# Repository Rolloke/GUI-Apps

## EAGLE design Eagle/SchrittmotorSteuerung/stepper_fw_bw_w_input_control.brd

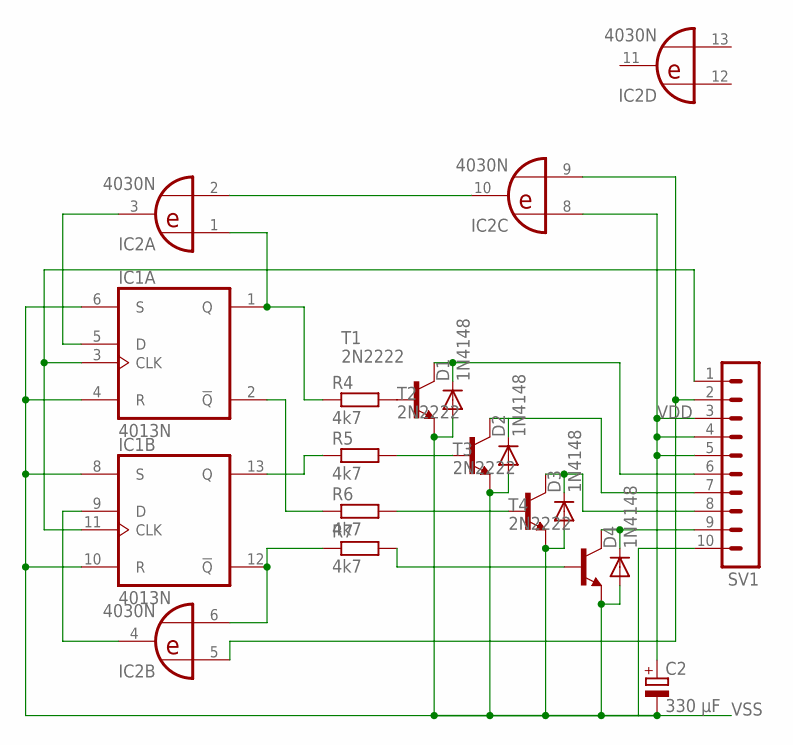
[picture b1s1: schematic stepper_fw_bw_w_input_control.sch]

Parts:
C2: 330 µF; E2,5-5
D1, D2, D3, D4: 1N4148; D-2.5
IC1: 4013N; DIL14
IC2: 4030N; DIL14
R4, R5, R6, R7: 4k7; 0207/10
SV1: MA10-1
T1, T2, T3, T4: 2N2222; TO18

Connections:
A1: D2.C, SV1.7, T2.3 (C)
A2: D1.C, SV1.6, T1.3 (C)
A3: D3.C, SV1.8, T3.3 (C)
A4: D4.C, SV1.9, T4.3 (C)
DIRECTION: IC2.5 (I0), IC2.9 (I1), SV1.2
unnamed: IC1.1 (Q), IC2.1 (I0), R4.1
unnamed: IC2.2 (I1), IC2.10 (O)
unnamed: IC1.2 (!Q), R6.1
unnamed: IC1.5 (D), IC2.3 (O)
unnamed: IC1.9 (D), IC2.4 (O)
unnamed: IC1.12 (!Q), IC2.6 (I1), R7.1
unnamed: IC1.13 (Q), R5.1
unnamed: R4.2, T1.2 (B)
unnamed: R5.2, T2.2 (B)
unnamed: R6.2, T3.2 (B)
unnamed: R7.2, T4.2 (B)
TACT: IC1.3 (CLK), IC1.11 (CLK), SV1.1
VDD: C2.+, IC1.14 (VDD), IC2.8 (I0), IC2.14 (VDD), SV1.3, SV1.4, SV1.5
VSS: C2.-, D1.A, D2.A, D3.A, D4.A, IC1.4 (R), IC1.6 (S), IC1.7 (VSS), IC1.8 (S), IC1.10 (R), IC2.7 (VSS), SV1.10, T1.1 (E), T2.1 (E), T3.1 (E), T4.1 (E)

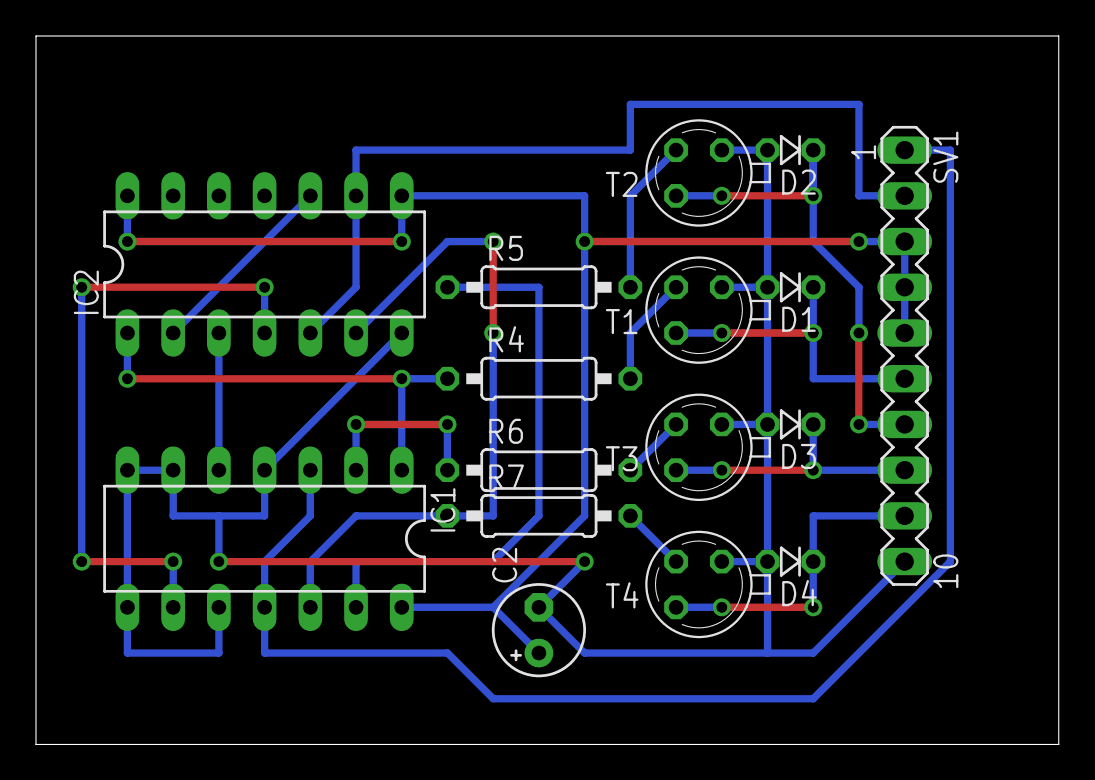
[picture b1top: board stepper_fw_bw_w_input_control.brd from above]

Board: 2 copper layers, 56.8 x 39.4 mm, 16 parts (0 on the bottom side), 19 nets.

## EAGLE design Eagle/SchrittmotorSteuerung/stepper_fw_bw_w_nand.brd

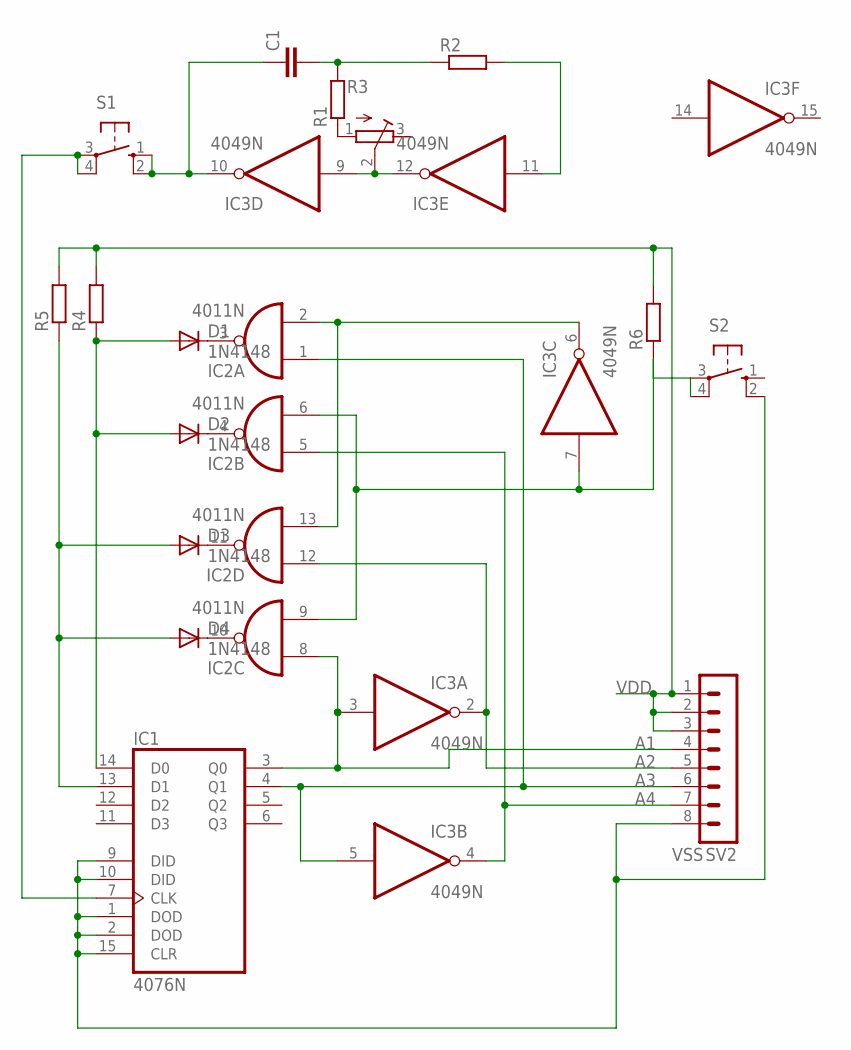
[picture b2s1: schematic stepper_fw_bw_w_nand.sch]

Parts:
C1: C-EU050-024X044; C050-024X044
D1, D2, D3, D4: 1N4148; DO35-7
IC1: 4076N; DIL16
IC2: 4011N; DIL14
IC3: 4049N; DIL16
R1, R2, R4, R5, R6: R-EU_0207/10; 0207/10
R3: R-TRIMM64W; RTRIM64W
S1, S2: 40-XX; B3F-40XX
SV2: MA08-1

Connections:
A1: IC1.3 (Q0), IC2.8 (I0), IC3.3 (I), SV2.4
A2: IC2.12 (I0), IC3.2 (O), SV2.5
A3: IC1.4 (Q1), IC2.1 (I0), IC3.5 (I), SV2.6
A4: IC2.5 (I0), IC3.4 (O), SV2.7
unnamed: IC3.9 (I), IC3.12 (O), R3.2 (S)
unnamed: IC1.7 (CLK), S1.3, S1.4 (P1)
unnamed: C1.2, R1.2, R2.1
unnamed: IC3.11 (I), R2.2
unnamed: C1.1, IC3.10 (O), S1.1 (S), S1.2 (S1)
unnamed: R1.1, R3.1 (A)
unnamed: IC2.2 (I1), IC2.13 (I1), IC3.6 (O)
unnamed: IC2.6 (I1), IC2.9 (I1), IC3.7 (I), R6.1, S2.3, S2.4 (P1)
unnamed: D1.C, IC2.3 (O)
unnamed: D2.C, IC2.4 (O)
unnamed: D3.C, IC2.11 (O)
unnamed: D4.C, IC2.10 (O)
unnamed: D3.A, D4.A, IC1.13 (D1), R5.1
unnamed: D1.A, D2.A, IC1.14 (D0), R4.1
VDD: IC1.16 (VDD), IC2.14 (VDD), IC3.1 (VDD), R4.2, R5.2, R6.2, SV2.1, SV2.2, SV2.3
VSS: IC1.1 (DOD), IC1.2 (DOD), IC1.8 (VSS), IC1.9 (DID), IC1.10 (DID), IC1.15 (CLR), IC2.7 (VSS), IC3.8 (VSS), S2.2 (S1), SV2.8

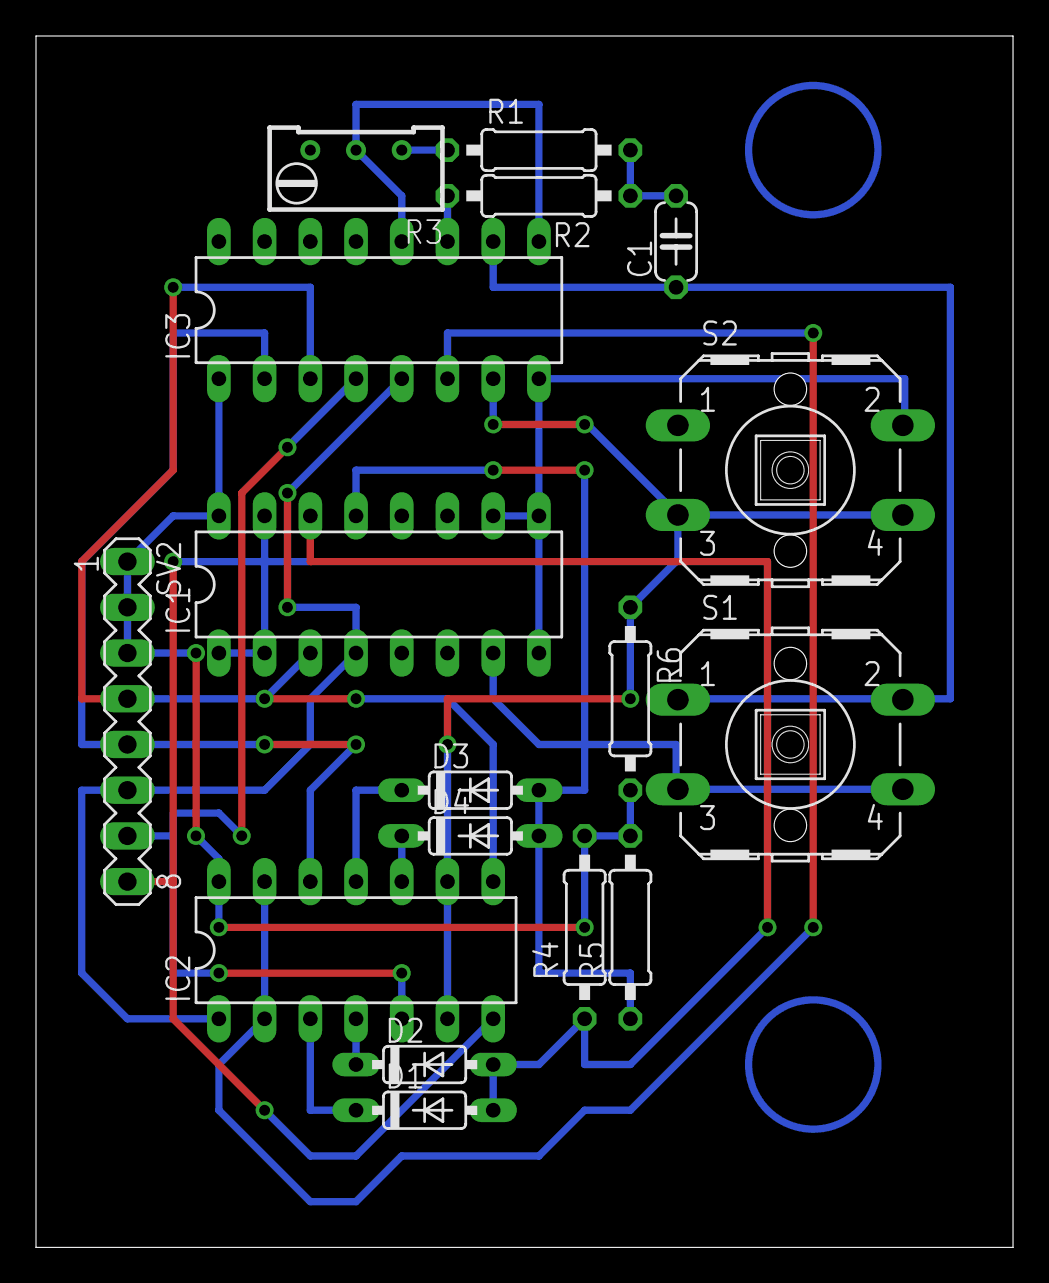
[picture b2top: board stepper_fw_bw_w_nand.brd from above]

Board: 2 copper layers, 54.3 x 67.3 mm, 17 parts (0 on the bottom side), 20 nets.

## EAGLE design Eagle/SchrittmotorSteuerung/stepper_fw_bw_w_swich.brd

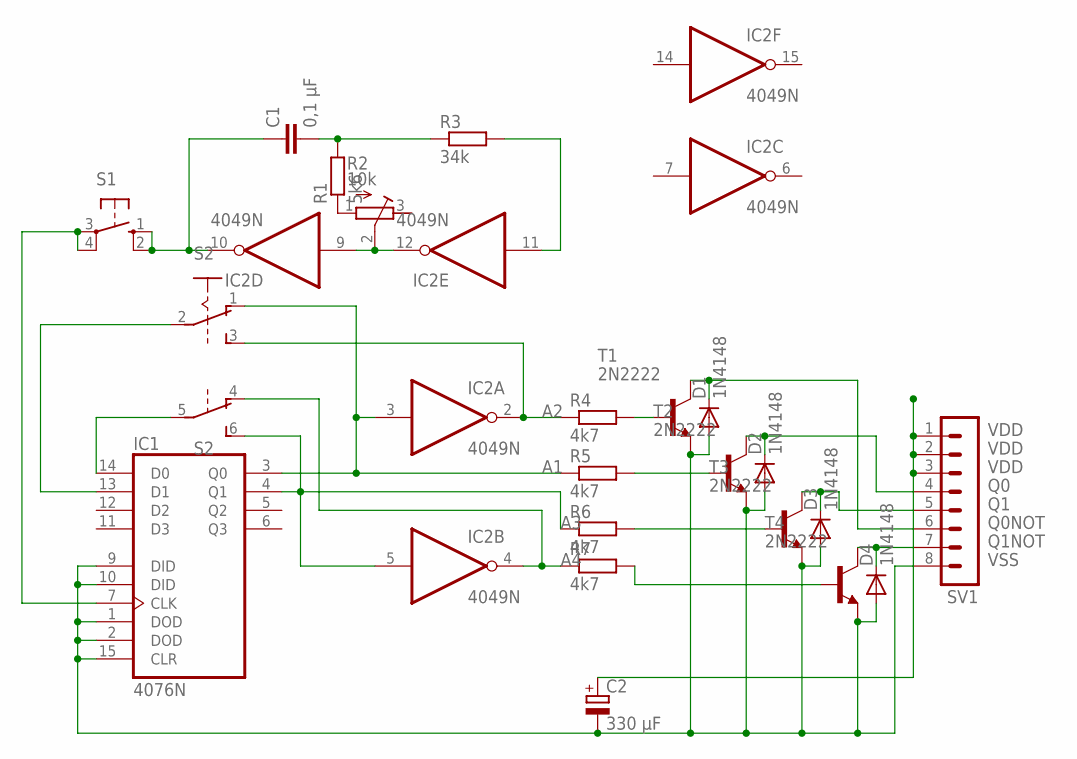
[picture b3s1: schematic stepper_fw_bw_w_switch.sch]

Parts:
C1: 0,1 µF; C050-024X044
C2: 330 µF; E2,5-5
D1, D2, D3, D4: 1N4148; D-2.5
IC1: 4076N; DIL16
IC2: 4049N; DIL16
R1: 5k6; 0207/10
R2: 10k; RTRIM64W
R3: 34k; 0207/10
R4, R5, R6, R7: 4k7; 0207/10
S1: 40-XX; B3F-40XX
S2: A68-A31
SV1: MA08-1
T1, T2, T3, T4: 2N2222; TO18

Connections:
A1: IC1.3 (Q0), IC2.3 (I), R5.1, S2.1 (O)
A2: IC2.2 (O), R4.1, S2.3 (S)
A3: IC1.4 (Q1), IC2.5 (I), R6.1, S2.6 (S)
A4: IC2.4 (O), R7.1, S2.4 (O)
unnamed: IC2.9 (I), IC2.12 (O), R2.2 (S)
unnamed: IC1.7 (CLK), S1.3, S1.4 (P1)
unnamed: C1.2, R1.2, R3.1
unnamed: IC2.11 (I), R3.2
unnamed: C1.1, IC2.10 (O), S1.1 (S), S1.2 (S1)
unnamed: R1.1, R2.1 (A)
unnamed: IC1.13 (D1), S2.2
unnamed: IC1.14 (D0), S2.5
unnamed: R4.2, T1.2 (B)
unnamed: R5.2, T2.2 (B)
unnamed: R6.2, T3.2 (B)
unnamed: R7.2, T4.2 (B)
Q0: D2.C, SV1.4, T2.3 (C)
Q0NOT: D1.C, SV1.6, T1.3 (C)
Q1: D3.C, SV1.5, T3.3 (C)
Q1NOT: D4.C, SV1.7, T4.3 (C)
VDD: C2.+, IC1.16 (VDD), IC2.1 (VDD), SV1.1, SV1.2, SV1.3
VSS: C2.-, D1.A, D2.A, D3.A, D4.A, IC1.1 (DOD), IC1.2 (DOD), IC1.8 (VSS), IC1.9 (DID), IC1.10 (DID), IC1.15 (CLR), IC2.8 (VSS), SV1.8, T1.1 (E), T2.1 (E), T3.1 (E), T4.1 (E)

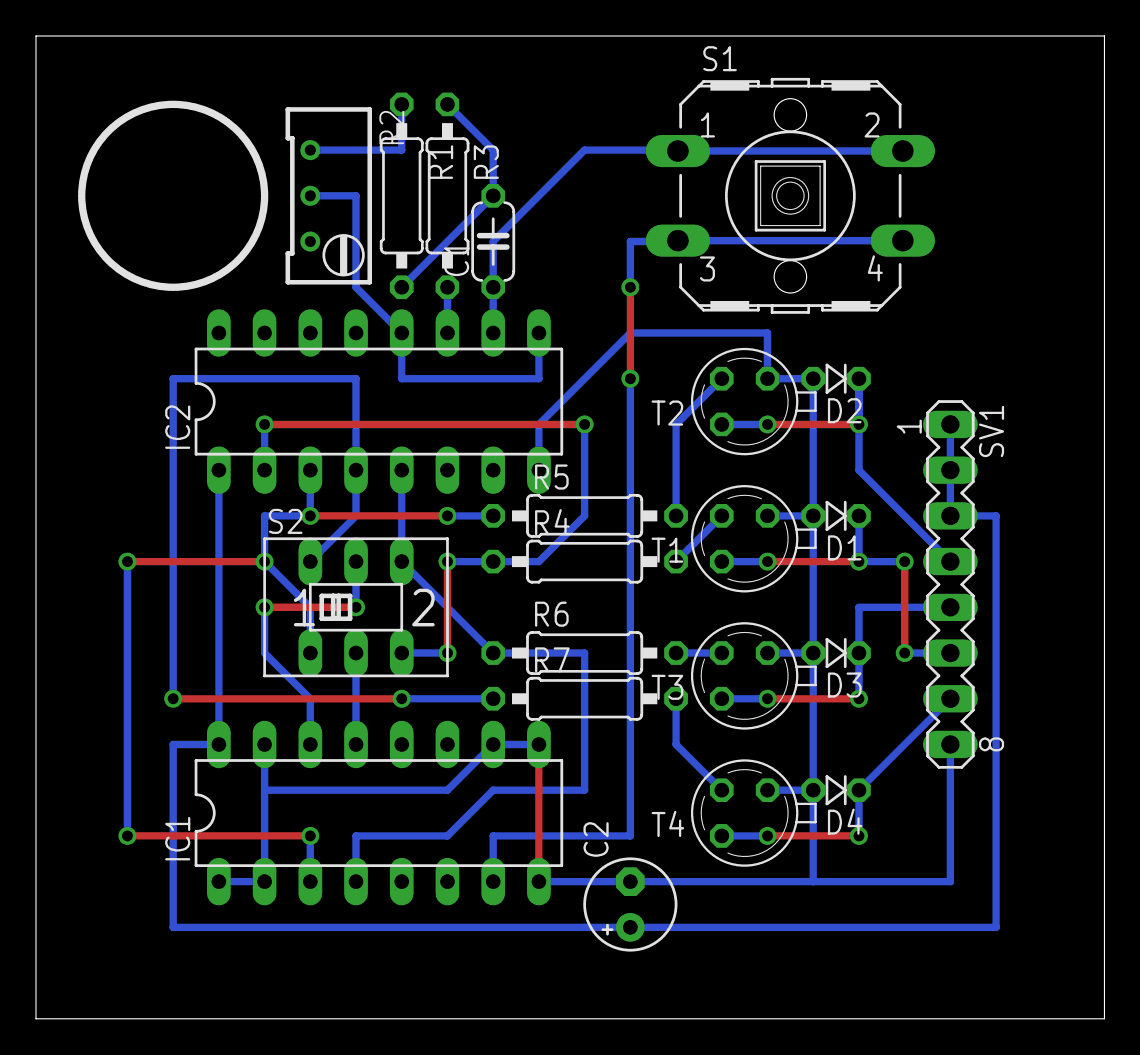
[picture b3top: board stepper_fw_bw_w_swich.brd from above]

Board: 2 copper layers, 59.4 x 54.6 mm, 22 parts (0 on the bottom side), 22 nets.

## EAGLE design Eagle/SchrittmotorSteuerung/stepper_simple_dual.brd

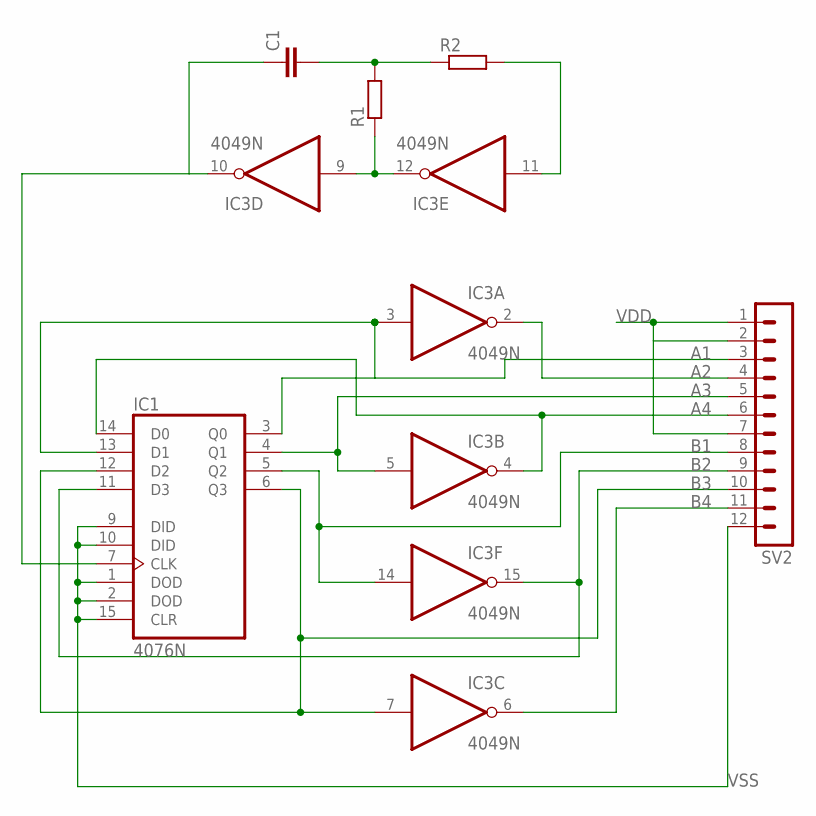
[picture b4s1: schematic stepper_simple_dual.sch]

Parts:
C1: C-EU050-024X044; C050-024X044
IC1: 4076N; DIL16
IC3: 4049N; DIL16
R1, R2: R-EU_0207/10; 0207/10
SV2: MA12-1

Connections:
A1: IC1.3 (Q0), IC1.13 (D1), IC3.3 (I), SV2.3
A2: IC3.2 (O), SV2.4
A3: IC1.4 (Q1), IC3.5 (I), SV2.5
A4: IC1.14 (D0), IC3.4 (O), SV2.6
B1: IC1.5 (Q2), IC3.14 (I)
B2: IC1.11 (D3), IC3.15 (O)
B3: IC1.6 (Q3), IC1.12 (D2), IC3.7 (I)
B4: IC3.6 (O)
unnamed: IC3.9 (I), IC3.12 (O), R1.1
unnamed: C1.1, IC1.7 (CLK), IC3.10 (O)
unnamed: C1.2, R1.2, R2.1
unnamed: IC3.11 (I), R2.2
VDD: IC1.16 (VDD), IC3.1 (VDD), SV2.1, SV2.2, SV2.7
VSS: IC1.1 (DOD), IC1.2 (DOD), IC1.8 (VSS), IC1.9 (DID), IC1.10 (DID), IC1.15 (CLR), IC3.8 (VSS)

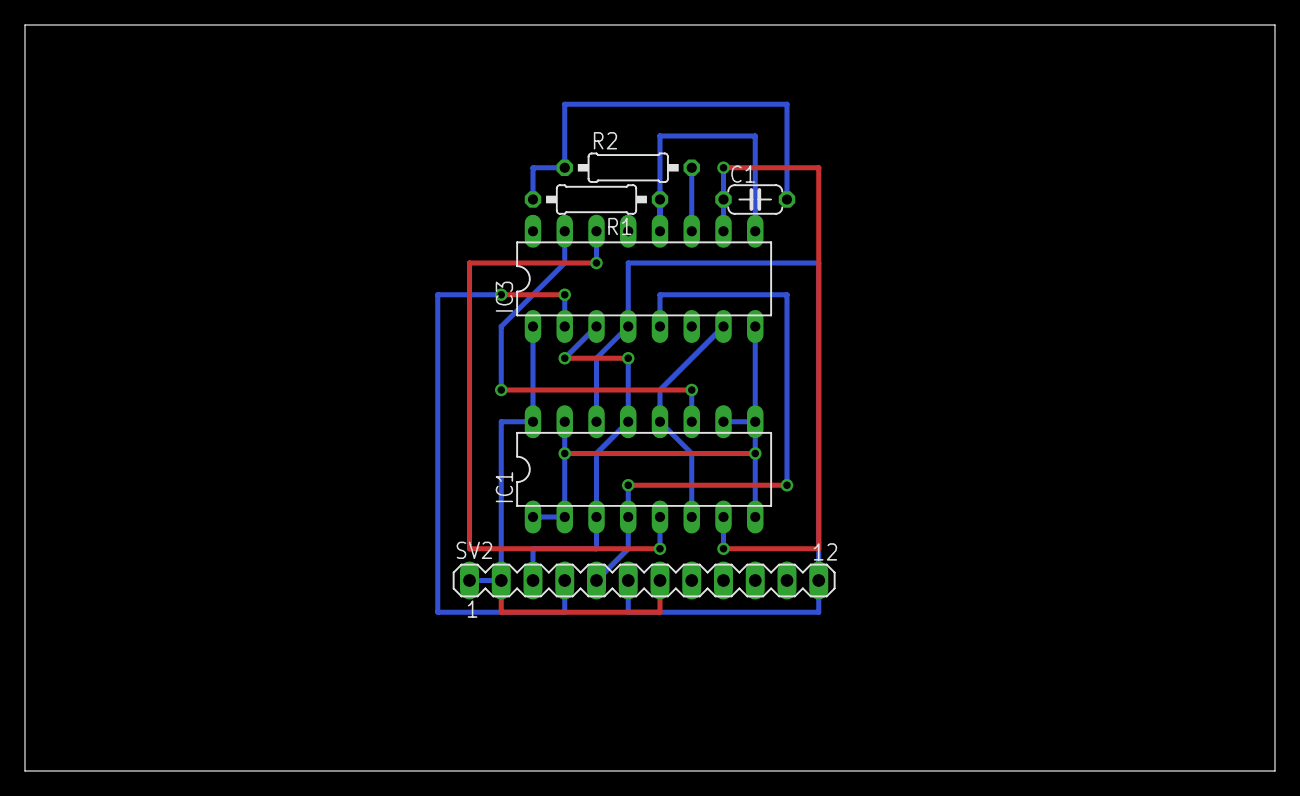
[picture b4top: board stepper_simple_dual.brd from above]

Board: 2 copper layers, 100.0 x 59.7 mm, 6 parts (0 on the bottom side), 13 nets.

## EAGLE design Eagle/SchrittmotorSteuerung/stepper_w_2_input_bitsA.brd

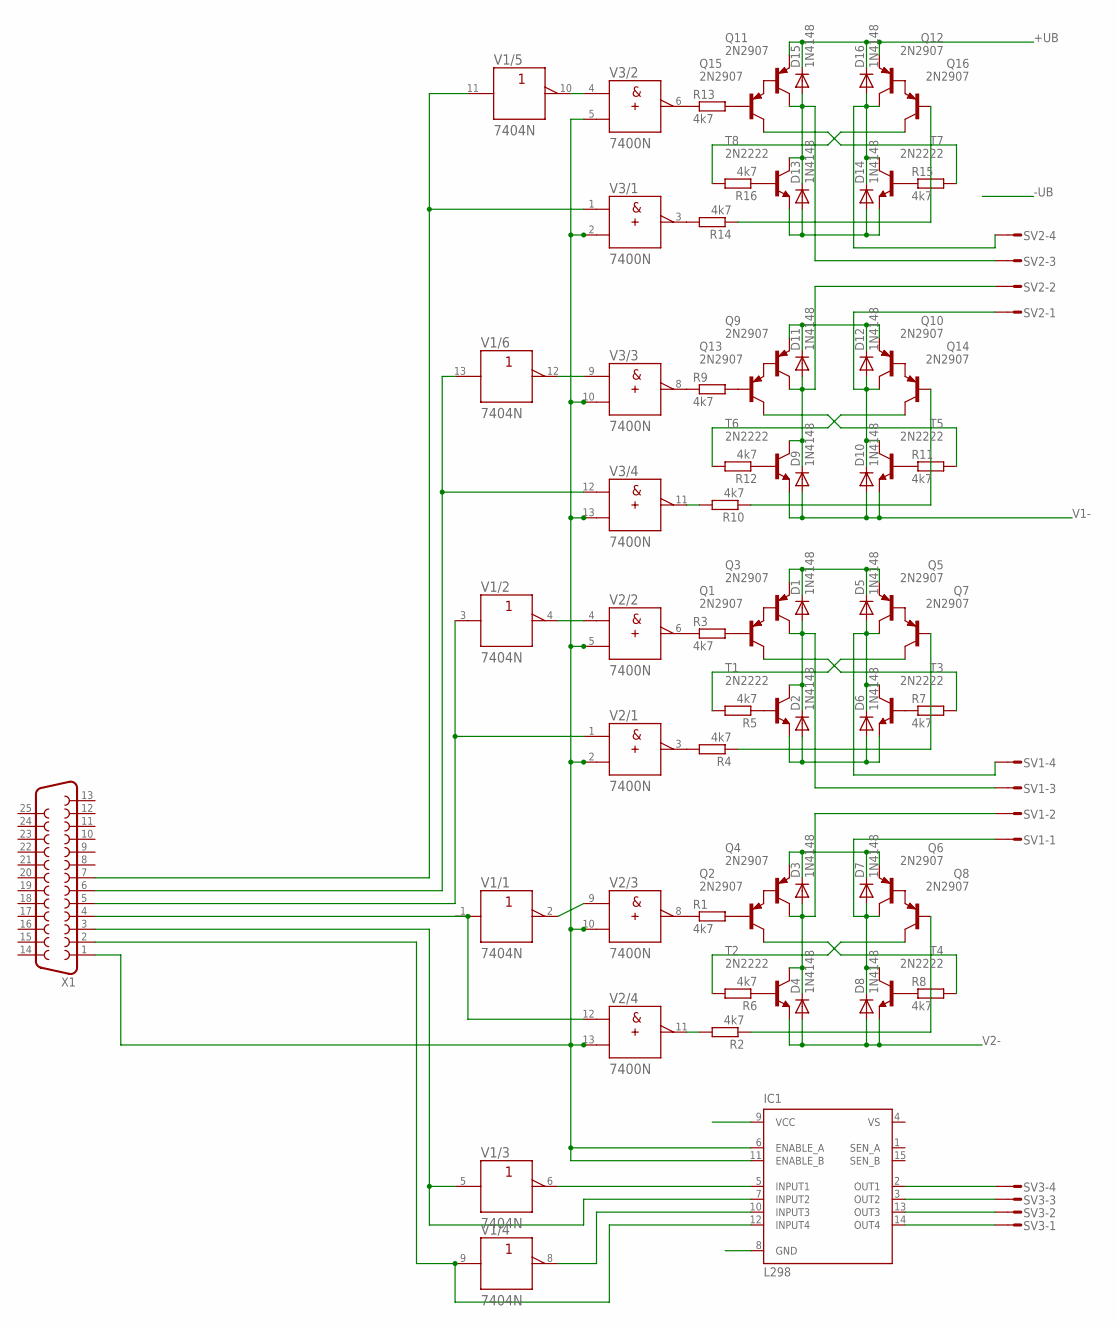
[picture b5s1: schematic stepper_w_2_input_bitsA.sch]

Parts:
D1, D2, D3, D4, D5, D6, D7, D8, D9, D10, D11, D12, D13, D14, D15, D16: 1N4148; D-2.5
IC1: L298; MULTIWATT-15
Q1, Q2, Q3, Q4, Q5, Q6, Q7, Q8, Q9, Q10, Q11, Q12, Q13, Q14, Q15, Q16: 2N2907; TO18
R1, R9: 4k7; 0204/7
R2, R3, R4, R5, R6, R7, R8, R10, R11, R12, R13, R14, R15, R16: 4k7; 0207/10
SV1, SV2, SV3: S04P
T1, T2, T3, T4, T5, T6, T7, T8: 2N2222; TO18
V1: 7404N; DIL14
V2, V3: 7400N; DIL14
X1: F25HP

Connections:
+UB: D1.C, D3.C, D5.C, D7.C, D11.C, D12.C, D15.C, D16.C, IC1.9 (VCC), Q3.1 (E), Q4.1 (E), Q5.1 (E), Q6.1 (E), Q9.1 (E), Q10.1 (E), Q11.1 (E), Q12.1 (E), V1.14 (+UB), V2.14 (+UB), V3.14 (+UB)
-UB: IC1.8 (GND), V1.7 (-UB), V2.7 (-UB), V3.7 (-UB)
unnamed: R6.1, T2.2 (B)
unnamed: Q8.3 (C), R6.2
unnamed: R8.1, T4.2 (B)
unnamed: Q2.2 (B), R1.2
unnamed: Q8.2 (B), R2.1
unnamed: Q2.1 (E), Q4.2 (B)
unnamed: Q2.3 (C), R8.2
unnamed: Q6.2 (B), Q8.1 (E)
unnamed: D3.A, D4.C, Q4.3 (C), SV1.2, T2.3 (C)
unnamed: D7.A, D8.C, Q6.3 (C), SV1.1, T4.3 (C)
unnamed: R1.1, V2.8 (Y)
unnamed: R2.2, V2.11 (Y)
unnamed: Q7.3 (C), R5.2
unnamed: V1.4 (Y), V2.4 (A)
unnamed: Q7.2 (B), R4.1
unnamed: R5.1, T1.2 (B)
unnamed: Q1.3 (C), R7.2
unnamed: R7.1, T3.2 (B)
unnamed: D1.A, D2.C, Q3.3 (C), SV1.3, T1.3 (C)
unnamed: D5.A, D6.C, Q5.3 (C), SV1.4, T3.3 (C)
unnamed: Q1.1 (E), Q3.2 (B)
unnamed: Q5.2 (B), Q7.1 (E)
unnamed: R4.2, V2.3 (Y)
unnamed: R3.1, V2.6 (Y)
unnamed: V1.3 (A), V2.1 (A), X1.5
unnamed: Q1.2 (B), R3.2
unnamed: V1.2 (Y), V2.9 (A)
unnamed: V1.1 (A), V2.12 (A), X1.4
unnamed: Q14.3 (C), R12.2
unnamed: Q14.2 (B), R10.1
unnamed: Q13.3 (C), R11.2
unnamed: D9.C, D11.A, Q9.3 (C), SV2.2, T6.3 (C)
unnamed: D10.C, D12.A, Q10.3 (C), SV2.1, T5.3 (C)
unnamed: R9.1, V3.8 (Y)
unnamed: R10.2, V3.11 (Y)
unnamed: Q16.3 (C), R16.2
unnamed: Q16.2 (B), R14.1
unnamed: Q15.3 (C), R15.2
unnamed: D13.C, D15.A, Q11.3 (C), SV2.3, T8.3 (C)
unnamed: D14.C, D16.A, Q12.3 (C), SV2.4, T7.3 (C)
unnamed: R14.2, V3.3 (Y)
unnamed: R13.1, V3.6 (Y)
unnamed: R12.1, T6.2 (B)
unnamed: R11.1, T5.2 (B)
unnamed: Q9.2 (B), Q13.1 (E)
unnamed: Q10.2 (B), Q14.1 (E)
unnamed: R16.1, T8.2 (B)
unnamed: R15.1, T7.2 (B)
unnamed: Q11.2 (B), Q15.1 (E)
unnamed: Q12.2 (B), Q16.1 (E)
unnamed: Q15.2 (B), R13.2
unnamed: V1.10 (Y), V3.4 (A)
unnamed: V1.11 (A), V3.1 (A), X1.7
unnamed: IC1.2 (OUT1), SV3.4
unnamed: V1.13 (A), V3.12 (A), X1.6
unnamed: Q13.2 (B), R9.2
unnamed: IC1.3 (OUT2), SV3.3
unnamed: IC1.13 (OUT3), SV3.2
unnamed: IC1.14 (OUT4), SV3.1
unnamed: IC1.5 (INPUT1), V1.6 (Y)
unnamed: IC1.7 (INPUT2), V1.5 (A), X1.3
unnamed: V1.12 (Y), V3.9 (A)
unnamed: IC1.12 (INPUT4), V1.9 (A), X1.2
unnamed: IC1.10 (INPUT3), V1.8 (Y)
STROBE: IC1.6 (ENABLE_A), IC1.11 (ENABLE_B), V2.2 (B), V2.5 (B), V2.10 (B), V2.13 (B), V3.2 (B), V3.5 (B), V3.10 (B), V3.13 (B), X1.1
V1-: D9.A, D10.A, D13.A, D14.A, T5.1 (E), T6.1 (E), T7.1 (E), T8.1 (E)
V2-: D2.A, D4.A, D6.A, D8.A, T1.1 (E), T2.1 (E), T3.1 (E), T4.1 (E)
VS: IC1.4 (VS)

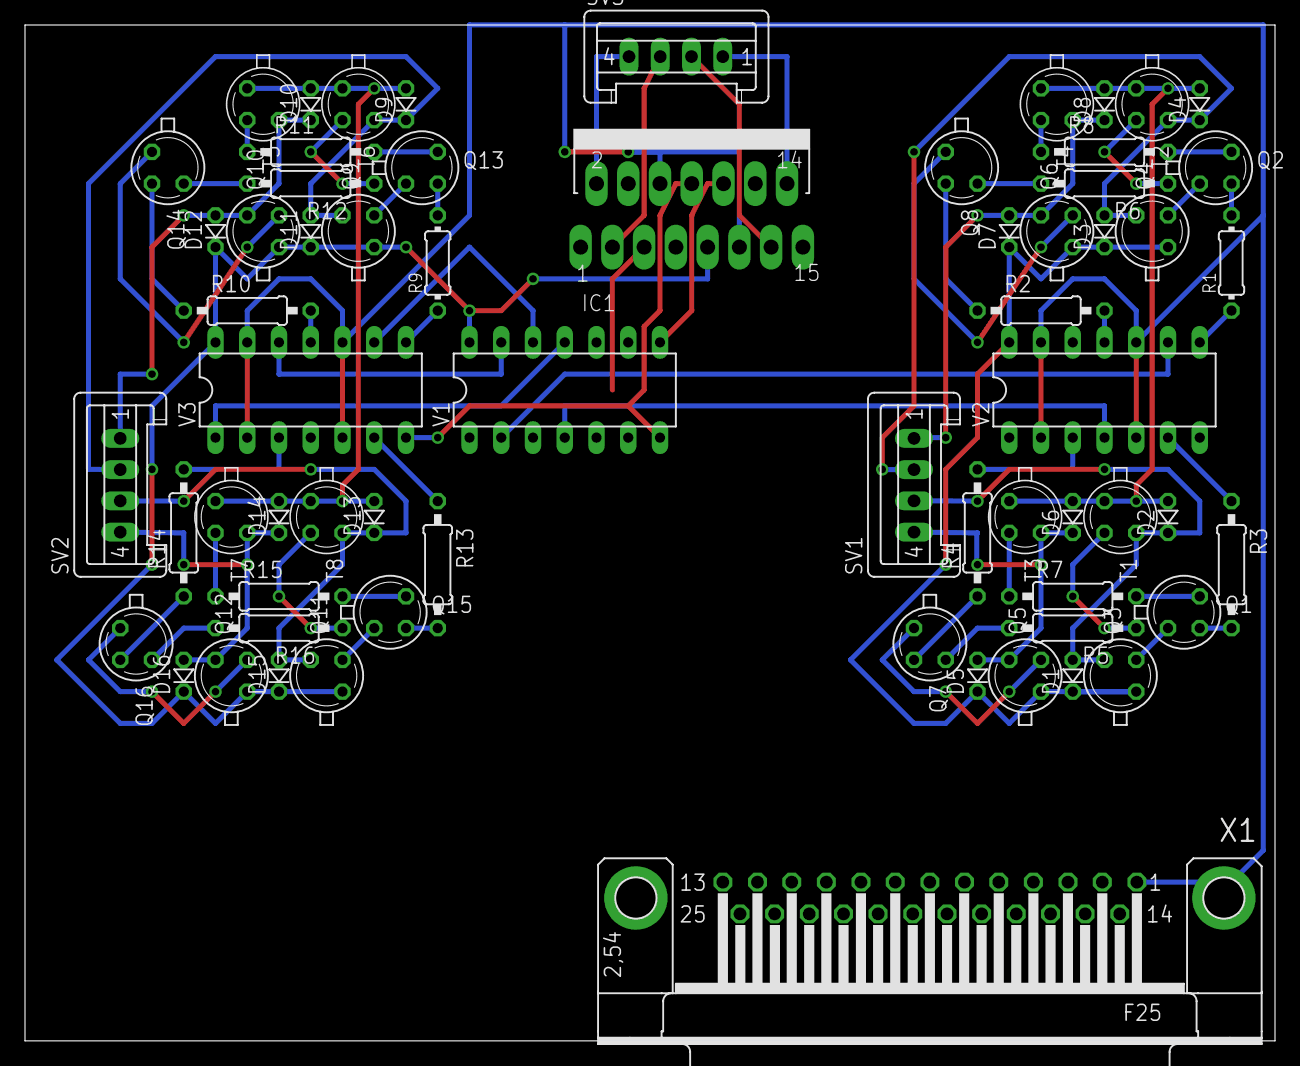
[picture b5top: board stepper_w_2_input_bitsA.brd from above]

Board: 2 copper layers, 100.0 x 81.3 mm, 64 parts (0 on the bottom side), 69 nets.

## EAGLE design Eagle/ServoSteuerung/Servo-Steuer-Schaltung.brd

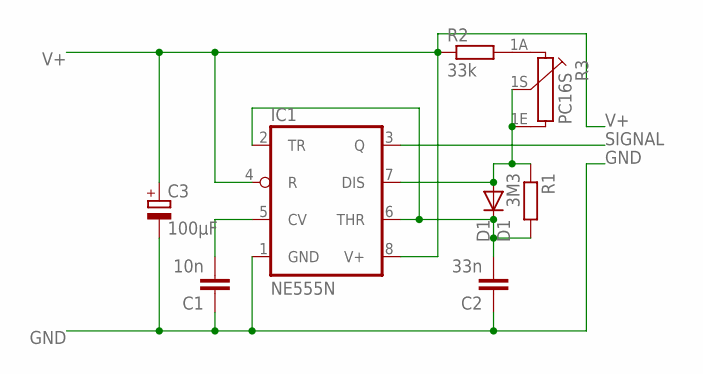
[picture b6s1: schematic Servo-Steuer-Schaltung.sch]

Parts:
C1: 10n; C10B4
C2: 33n; C10B4
C3: 100µF; E2,5-7
D1: D1; DO35-7
IC1: NE555N; DIL08
R1: 3M3; 0207/10
R2: 33k; 0207/10
R3: PC16S

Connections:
GND: C1.1, C2.1, C3.-, IC1.1 (GND)
unnamed: R2.2, R3.1A
unnamed: D1.A, IC1.7 (DIS), R1.1, R3.1E, R3.1S
unnamed: C2.2, D1.C, IC1.2 (TR), IC1.6 (THR), R1.2
unnamed: C1.2, IC1.5 (CV)
SIGNAL: IC1.3 (Q)
V+: C3.+, IC1.4 (R), IC1.8 (V+), R2.1

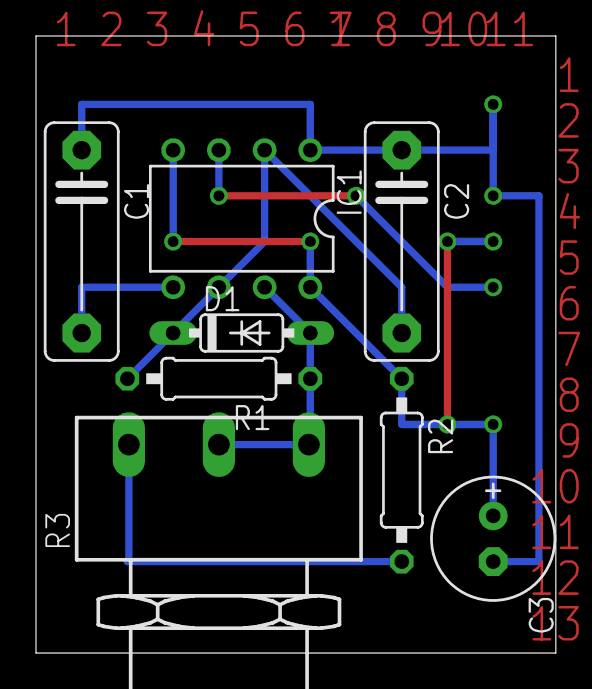
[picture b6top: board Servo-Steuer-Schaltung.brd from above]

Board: 2 copper layers, 28.9 x 34.3 mm, 8 parts (0 on the bottom side), 6 nets.
